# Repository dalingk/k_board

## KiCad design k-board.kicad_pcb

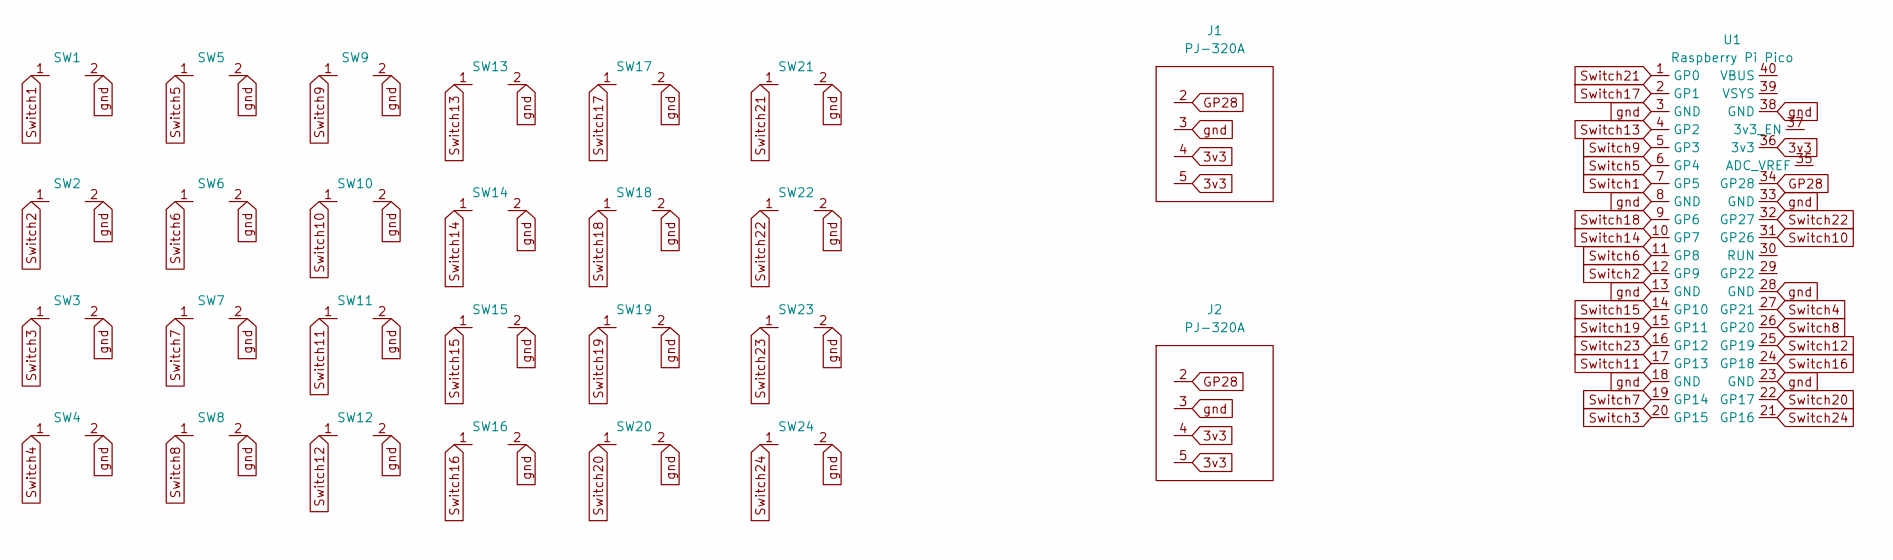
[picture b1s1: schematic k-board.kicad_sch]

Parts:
J1, J2: PJ-320A
SW1, SW2, SW3, SW4, SW5, SW6, SW7, SW8, SW9, SW10, SW11, SW12, SW13, SW14, SW15, SW16, SW17, SW18, SW19, SW20, SW21, SW22, SW23, SW24: Cherry MX
U1: Raspberry Pi Pico

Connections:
3v3: J1.4, J1.5, J2.4, J2.5, U1.36 (3v3)
GP28: J1.2, J2.2, U1.34 (GP28)
Switch1: SW1.1, U1.7 (GP5)
Switch2: SW2.1, U1.12 (GP9)
Switch3: SW3.1, U1.20 (GP15)
Switch4: SW4.1, U1.27 (GP21)
Switch5: SW5.1, U1.6 (GP4)
Switch6: SW6.1, U1.11 (GP8)
Switch7: SW7.1, U1.19 (GP14)
Switch8: SW8.1, U1.26 (GP20)
Switch9: SW9.1, U1.5 (GP3)
Switch10: SW10.1, U1.31 (GP26)
Switch11: SW11.1, U1.17 (GP13)
Switch12: SW12.1, U1.25 (GP19)
Switch13: SW13.1, U1.4 (GP2)
Switch14: SW14.1, U1.10 (GP7)
Switch15: SW15.1, U1.14 (GP10)
Switch16: SW16.1, U1.24 (GP18)
Switch17: SW17.1, U1.2 (GP1)
Switch18: SW18.1, U1.9 (GP6)
Switch19: SW19.1, U1.15 (GP11)
Switch20: SW20.1, U1.22 (GP17)
Switch21: SW21.1, U1.1 (GP0)
Switch22: SW22.1, U1.32 (GP27)
Switch23: SW23.1, U1.16 (GP12)
Switch24: SW24.1, U1.21 (GP16)
gnd: J1.3, J2.3, SW1.2, SW2.2, SW3.2, SW4.2, SW5.2, SW6.2, SW7.2, SW8.2, SW9.2, SW10.2, SW11.2, SW12.2, SW13.2, SW14.2, SW15.2, SW16.2, SW17.2, SW18.2, SW19.2, SW20.2, SW21.2, SW22.2, SW23.2, SW24.2, U1.3 (GND), U1.8 (GND), U1.13 (GND), U1.18 (GND), U1.23 (GND), U1.28 (GND), U1.33 (GND), U1.38 (GND)

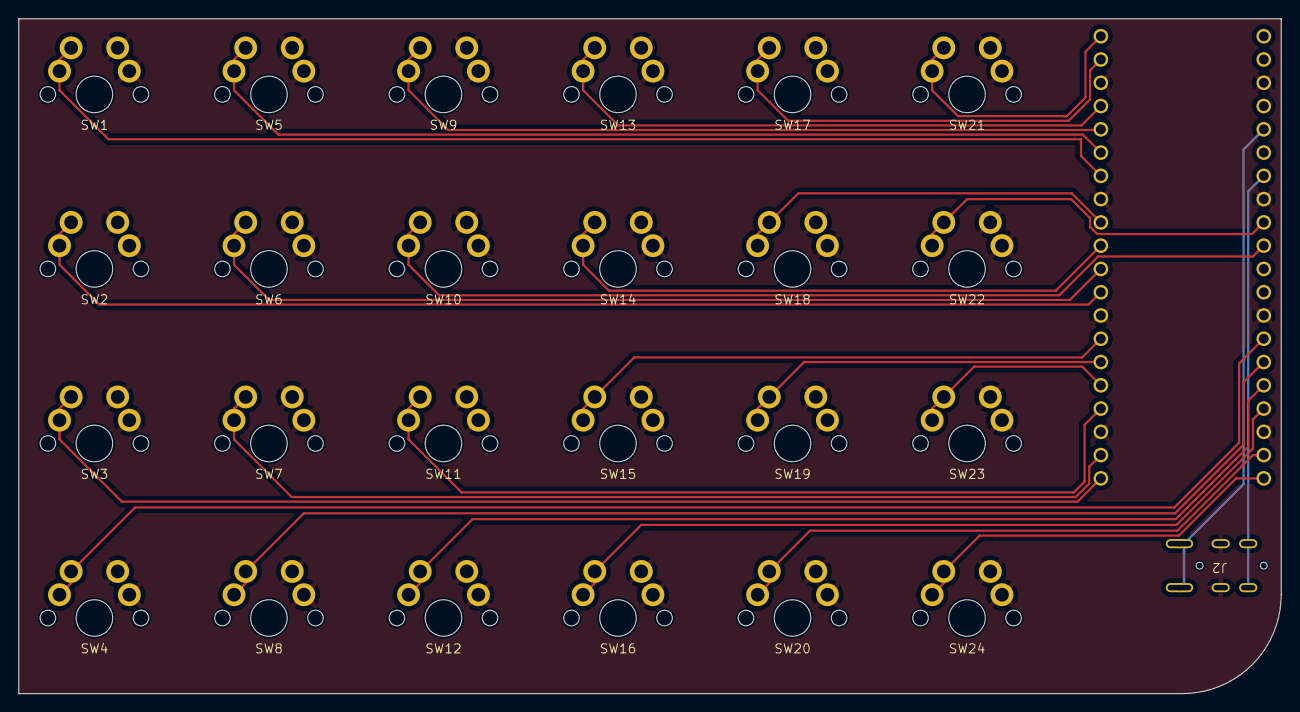
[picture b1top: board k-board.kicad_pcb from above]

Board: 2 copper layers, 137.8 x 73.7 mm, 27 parts (1 on the bottom side), 27 nets.

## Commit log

2023-08-20 Commit v1.0 board
